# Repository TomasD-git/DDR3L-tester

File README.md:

# DDR3L-tester  
**Very simple DDR3L tester, plug ddr3l stick into slot, esp32 c6 reads data and can overwrite config of ram as well, with buttons for control and screen to see progress**  

<details>
<summary>How to make one?</summary>
  
**Either buy PCBA which is much easier but much more expenisve, or buy all parts and assemble with hotplate or hotair gun. all files needed for this are in production folder**  

</details>

<details>
<summary>How assemble?</summary>
Place top part ontop of the pcb and solder screen and buttons, then place the bottom part underneath the pcb and use M2 screws to screw into place.  

</details>

<details>
<summary>How to flash?</summary>
Plug the USB-C into computer and use arduino ide to flash.  

</details>

<details>
<summary>BOM</summary>

| Name | Purpose | Quantity | Total Cost (USD) | Link | Distributor |
| --- | --- | --- | --- | --- | --- |
| PCB + stencil if needed | all components are on this | 1 | 20 | https://jlcpcb.com | jlcpcb |
| ALL components | all components that are on pcb | 1 | 40 | https://lcsc.com | lcsc |
| Screen | shows info numbers etc.. | 1 | 3 | https://www.aliexpress.com/item/1005006141235306.html | Aliexpress |
| | | **Total cost** | **63** | | |

</details>

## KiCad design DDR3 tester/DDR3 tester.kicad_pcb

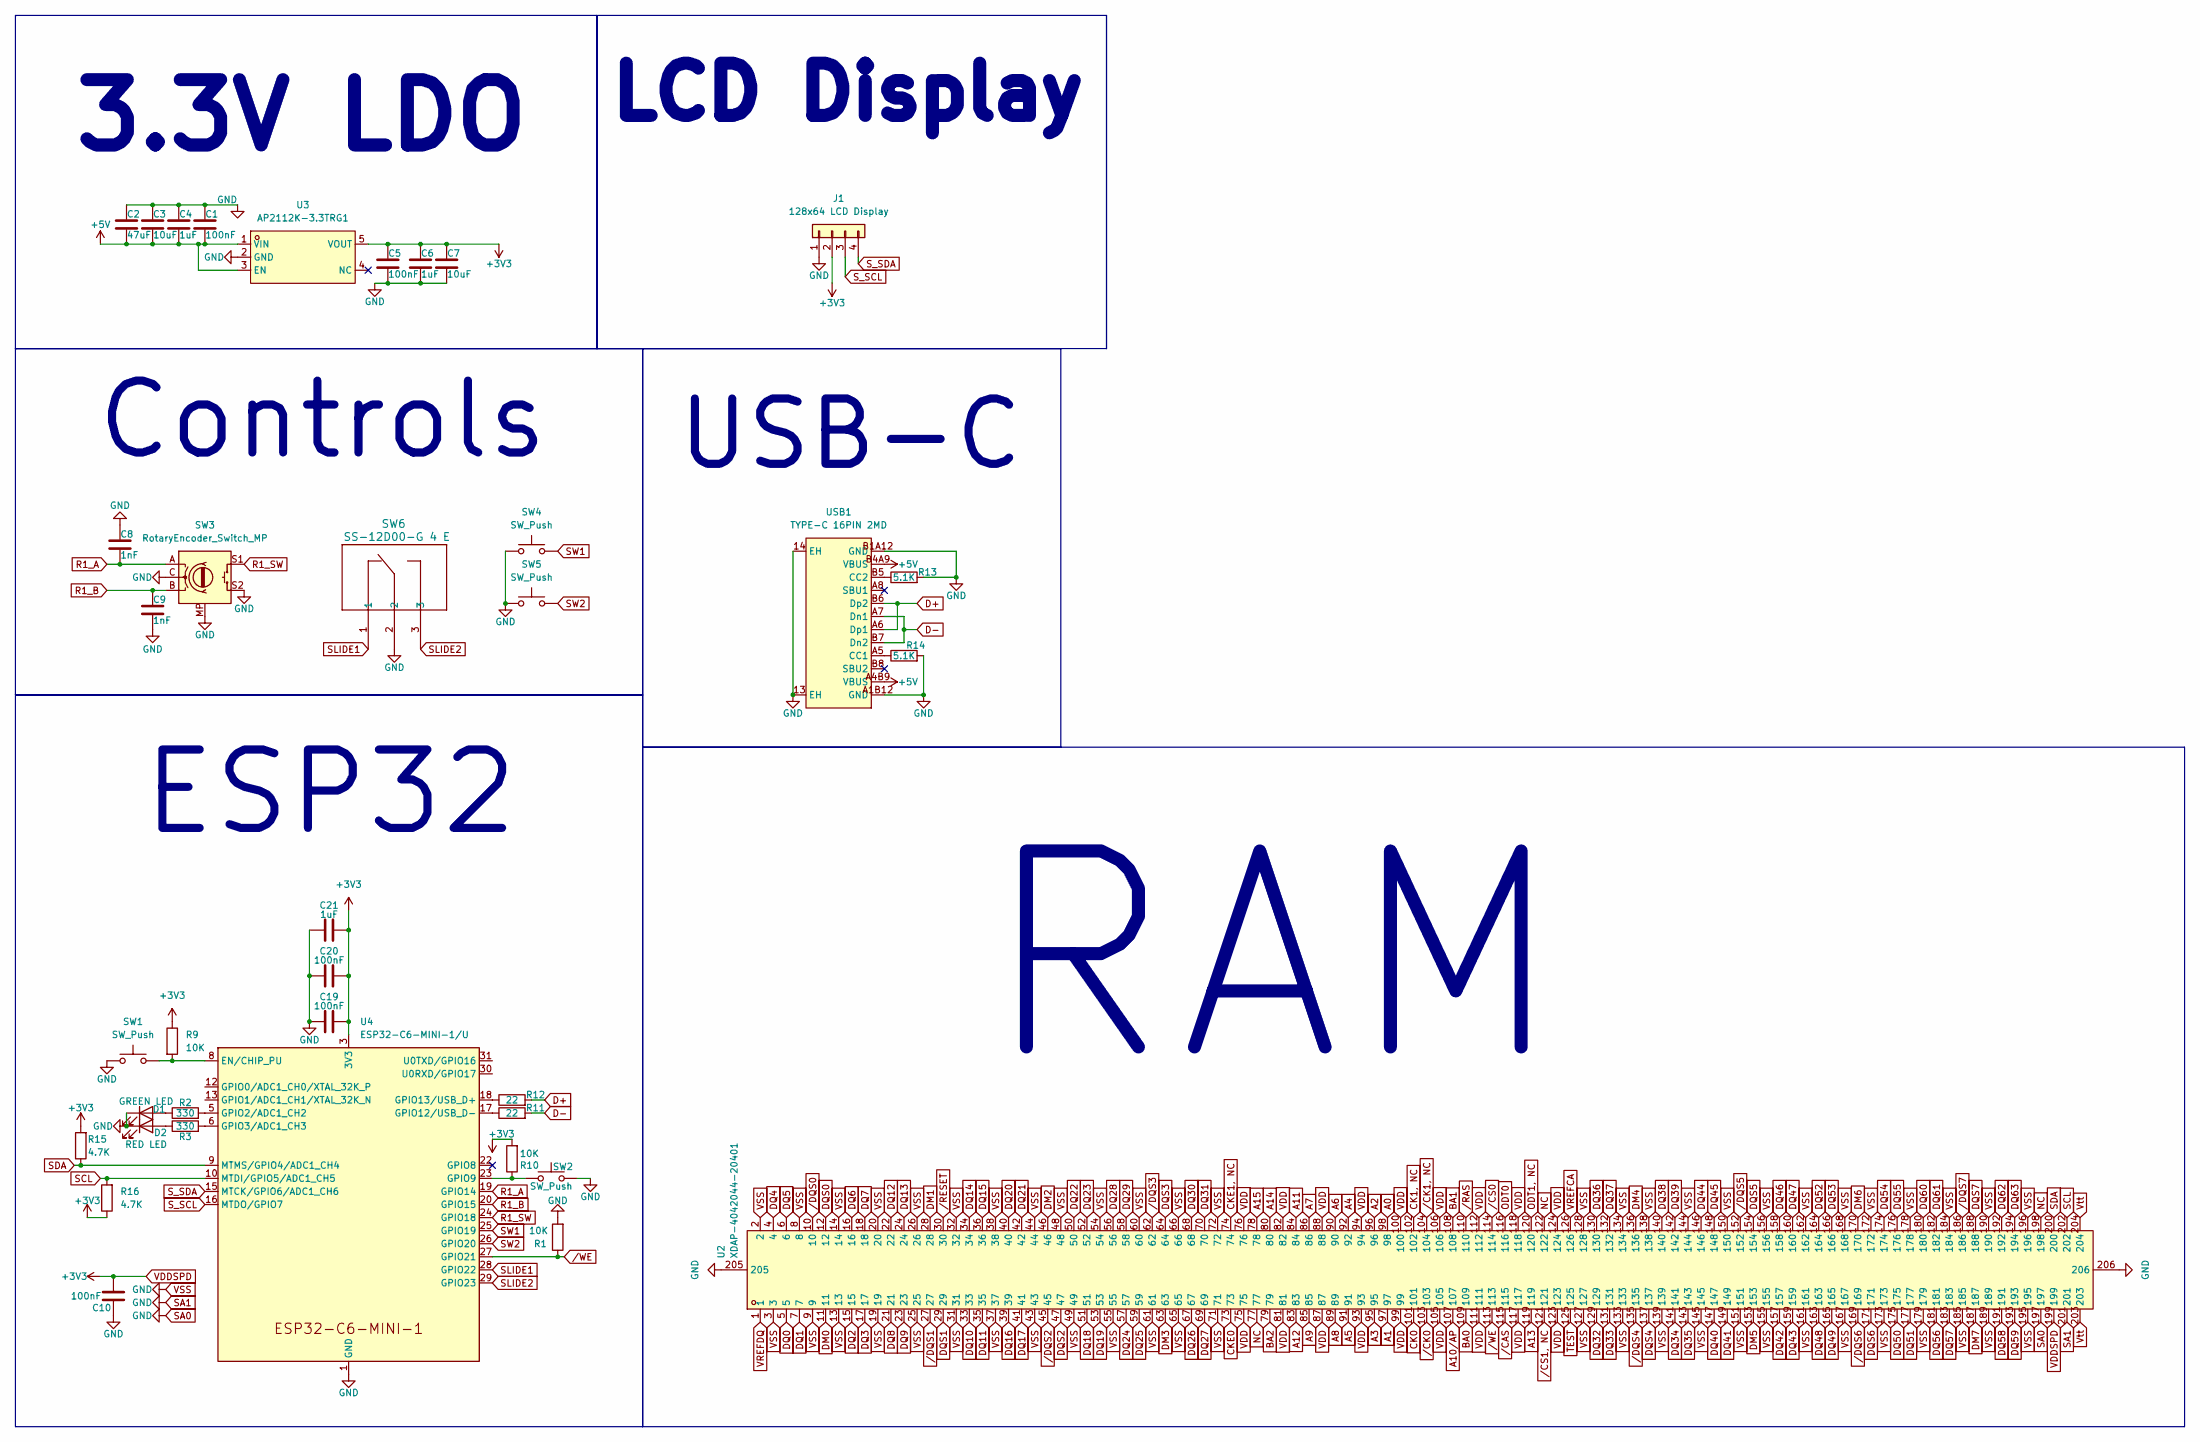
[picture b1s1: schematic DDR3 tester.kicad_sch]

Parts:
C1, C5, C10, C19, C20: 100nF; C_0805_2012Metric
C2: 47uF; C_1210_3225Metric
C3, C7: 10uF; C_0805_2012Metric
C4, C6, C21: 1uF; C_0805_2012Metric
C8, C9: 1nF; C_0805_2012Metric
D1: GREEN LED; LED_D5.0mm
D2: RED LED; LED_D5.0mm
J1: 128x64 LCD Display; PinSocket_1x04_P2.54mm_Vertical
R1, R9, R10: 10K; R_0805_2012Metric
R2, R3: 330; R_0805_2012Metric
R11, R12: 22; R_0805_2012Metric
R13, R14: 5.1K; R_0805_2012Metric
R15, R16: 4.7K; R_0805_2012Metric
SW1, SW2: SW_Push; SW_PUSH_6mm
SW3: RotaryEncoder_Switch_MP; RotaryEncoder_Alps_EC11E-Switch_Vertical_H20mm
SW4, SW5: SW_Push; SW_Cherry_MX_1.00u_PCB
SW6: SS-12D00-G 4 E; 1P2T_SS-12D00_CNK
U2: XDAP-4042044-20401; CONN-SMD_204P-P0.60_XDAP-4042044-20401; MPN XDAP-4042044-20401; LCSC Part C22471982
U3: AP2112K-3.3TRG1; SOT-25-5_L2.9-W1.6-P0.95-LS2.8-BL; MPN AP2112K-3.3TRG1; LCSC Part C51118
U4: ESP32-C6-MINI-1/U; ESP32-C6-MINI-1
USB1: TYPE-C 16PIN 2MD; USB-C-SMD_TYPE-C-16PIN-2MD-073; MPN TYPE-C 16PIN 2MD(073); LCSC Part C2765186

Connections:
+5V: C1.2, C2.1, C3.1, C4.2, U3.1 (VIN), U3.3 (EN), USB1.A4B9 (VBUS), USB1.B4A9 (VBUS)
A0: U2.98
A1: U2.97
A2: U2.96
A3: U2.95
A4: U2.92
A5: U2.91
A6: U2.90
A7: U2.86
A8: U2.89
A9: U2.85
A10/AP: U2.107
A11: U2.84
A12: U2.83
A13: U2.119
A14: U2.80
A15: U2.78
BA0: U2.109
BA1: U2.108
BA2: U2.79
CK0: U2.101
CK1, NC: U2.102
CKE0: U2.73
CKE1, NC: U2.74
D+: R12.2, USB1.A6 (Dp1), USB1.B6 (Dp2)
D-: R11.2, USB1.A7 (Dn1), USB1.B7 (Dn2)
DM0: U2.11
DM1: U2.28
DM2: U2.46
DM3: U2.63
DM4: U2.136
DM5: U2.153
DM6: U2.170
DM7: U2.187
DQ0: U2.5
DQ1: U2.7
DQ2: U2.15
DQ3: U2.17
DQ4: U2.4
DQ5: U2.6
DQ6: U2.16
DQ7: U2.18
DQ8: U2.21
DQ9: U2.23
DQ10: U2.33
DQ11: U2.35
DQ12: U2.22
DQ13: U2.24
DQ14: U2.34
DQ15: U2.36
DQ16: U2.39
DQ17: U2.41
DQ18: U2.51
DQ19: U2.53
DQ20: U2.40
DQ21: U2.42
DQ22: U2.50
DQ23: U2.52
DQ24: U2.57
DQ25: U2.59
DQ26: U2.67
DQ27: U2.69
DQ28: U2.56
DQ29: U2.58
DQ30: U2.68
DQ31: U2.70
DQ32: U2.129
DQ33: U2.131
DQ34: U2.141
DQ35: U2.143
DQ36: U2.130
DQ37: U2.132
DQ38: U2.140
DQ39: U2.142
DQ40: U2.147
DQ41: U2.149
DQ42: U2.157
DQ43: U2.159
DQ44: U2.146
DQ45: U2.148
DQ46: U2.158
DQ47: U2.160
DQ48: U2.163
DQ49: U2.165
DQ50: U2.175
DQ51: U2.177
DQ52: U2.164
DQ53: U2.166
DQ54: U2.174
DQ55: U2.176
DQ56: U2.181
DQ57: U2.183
DQ58: U2.191
DQ59: U2.193
DQ60: U2.180
DQ61: U2.182
DQ62: U2.192
DQ63: U2.194
DQS0: U2.12
DQS1: U2.29
DQS2: U2.47
DQS3: U2.64
DQS4: U2.137
DQS5: U2.154
DQS6: U2.171
DQS7: U2.188
NC: U2.77, U2.122, U2.198
unnamed: D1.2 (A), R2.1
unnamed: D2.2 (A), R3.1
unnamed: R9.2, SW1.2, U4.8 (EN/CHIP_PU)
unnamed: R2.2, U4.5 (GPIO2/ADC1_CH2)
unnamed: R3.2, U4.6 (GPIO3/ADC1_CH3)
unnamed: R10.1, SW2.1, U4.23 (GPIO9)
unnamed: R11.1, U4.17 (GPIO12/USB_D-)
unnamed: R12.1, U4.18 (GPIO13/USB_D+)
unnamed: R14.1, USB1.A5 (CC1)
unnamed: R13.1, USB1.B5 (CC2)
ODT0: U2.116
ODT1, NC: U2.120
R1_A: C8.2, SW3.A, U4.19 (GPIO14)
R1_B: C9.1, SW3.B, U4.20 (GPIO15)
R1_SW: SW3.S1, U4.24 (GPIO18)
SA0: C1.1, C2.2, C3.2, C4.1, C5.2, C6.2, C7.2, C8.1, C9.2, C10.1, C19.1, C20.1, C21.1, D1.1 (K), D2.1 (K), J1.1, R1.2, R13.2, R14.2, SW1.1, SW2.2, SW3.C, SW3.MP, SW3.S2, SW4.1, SW5.1, SW6.2, U2.2, U2.3, U2.8, U2.9, U2.13, U2.14, U2.19, U2.20, U2.25, U2.26, U2.31, U2.32, U2.37, U2.38, U2.43, U2.44, U2.48, U2.49, U2.54, U2.55, U2.60, U2.61, U2.65, U2.66, U2.71, U2.72, U2.127, U2.128, U2.133, U2.134, U2.138, U2.139, U2.144, U2.145, U2.150, U2.151, U2.155, U2.156, U2.161, U2.162, U2.167, U2.168, U2.172, U2.173, U2.178, U2.179, U2.184, U2.185, U2.189, U2.190, U2.195, U2.196, U2.197, U2.201, U2.205, U2.206, U3.2 (GND), U4.1 (GND), U4.2 (GND), U4.11 (GND), U4.14 (GND), U4.36 (GND), U4.37 (GND), U4.38 (GND), U4.39 (GND), U4.40 (GND), U4.41 (GND), U4.42 (GND), U4.43 (GND), U4.44 (GND), U4.45 (GND), U4.46 (GND), U4.47 (GND), U4.48 (GND), U4.49 (GND), U4.50 (GND), U4.51 (GND), U4.52 (GND), U4.53 (GND), USB1.13 (EH), USB1.14 (EH), USB1.A1B12 (GND), USB1.B1A12 (GND)
SCL: R16.2, U2.202, U4.10 (MTDI/GPIO5/ADC1_CH5)
SDA: R15.1, U2.200, U4.9 (MTMS/GPIO4/ADC1_CH4)
SLIDE1: SW6.1, U4.28 (GPIO22)
SLIDE2: SW6.3, U4.29 (GPIO23)
SW1: SW4.2, U4.25 (GPIO19)
SW2: SW5.2, U4.26 (GPIO20)
S_SCL: J1.3, U4.16 (MTDO/GPIO7)
S_SDA: J1.4, U4.15 (MTCK/GPIO6/ADC1_CH6)
TEST: U2.125
VDD: U2.75, U2.76, U2.81, U2.82, U2.87, U2.88, U2.93, U2.94, U2.99, U2.100, U2.105, U2.106, U2.111, U2.112, U2.117, U2.118, U2.123, U2.124
VDDSPD: C5.1, C6.1, C7.1, C10.2, C19.2, C20.2, C21.2, J1.2, R9.1, R10.2, R15.2, R16.1, U2.199, U3.5 (VOUT), U4.3 (3V3)
VREFCA: U2.126
VREFDQ: U2.1
Vtt: U2.203, U2.204
/CAS: U2.115
/CK0: U2.103
/CK1, NC: U2.104
/CS0: U2.114
/CS1, NC: U2.121
/DQS0: U2.10
/DQS1: U2.27
/DQS2: U2.45
/DQS3: U2.62
/DQS4: U2.135
/DQS5: U2.152
/DQS6: U2.169
/DQS7: U2.186
/RAS: U2.110
/RESET: U2.30
/WE: R1.1, U2.113, U4.27 (GPIO21)

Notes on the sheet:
RAM
LCD Display
Controls
USB-C
3.3V LDO
ESP32

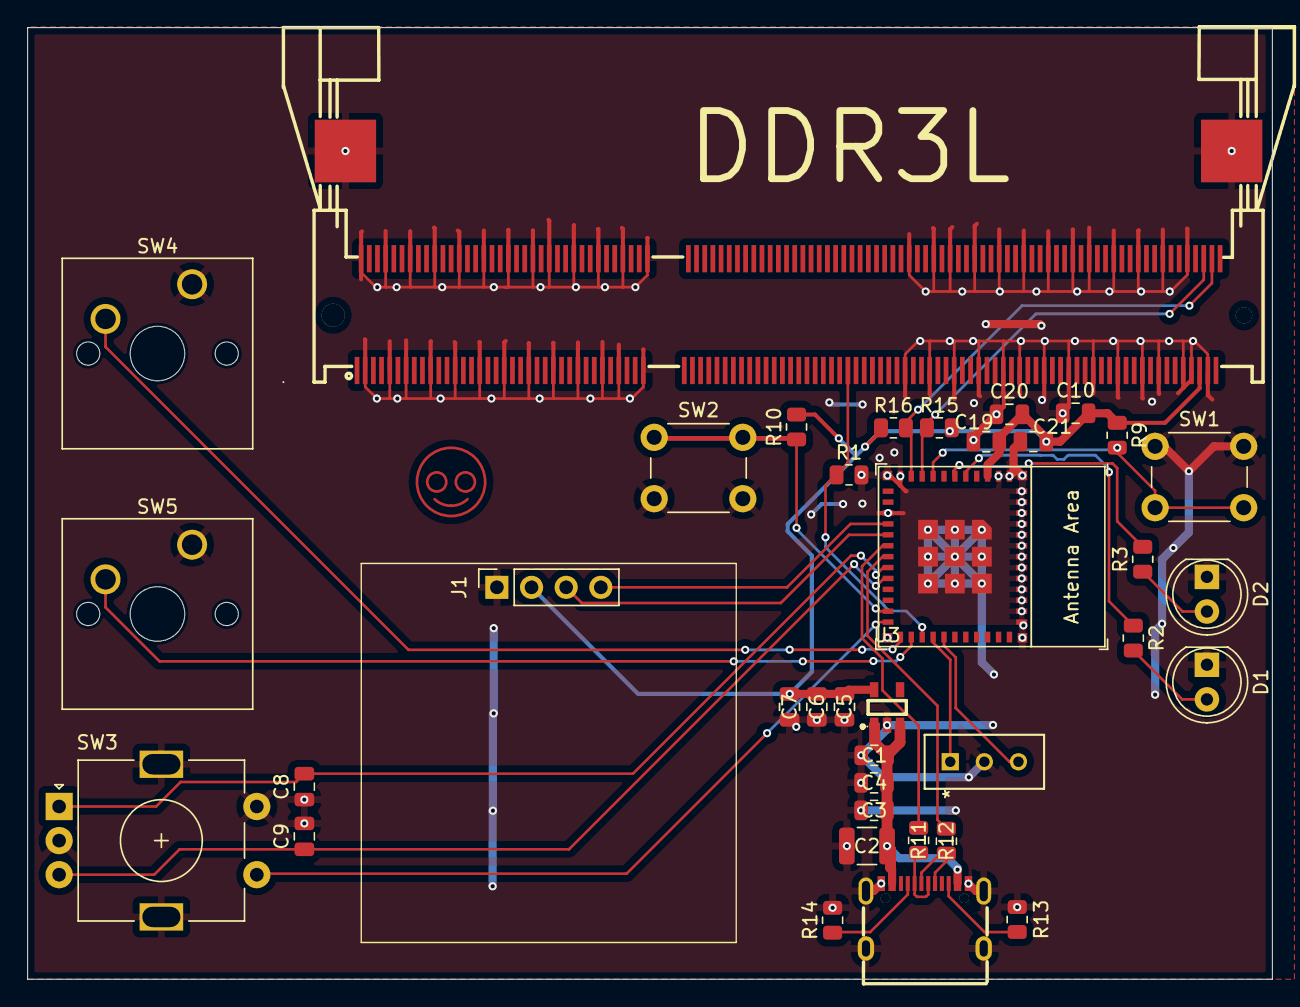
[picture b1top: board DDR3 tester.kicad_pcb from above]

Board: 2 copper layers, 91.3 x 69.8 mm, 37 parts (0 on the bottom side), 30 nets.

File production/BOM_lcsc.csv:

JLCPCB BOM Tool - BOM Matching,,,,,,,,,,,,,,,,,
BOM name：bom-JLCPCB Assembly Order.xlsx,,,Download Time：2026-06-09 15:07:55,,,,"* Our matching results are updated in real-time, but stock and prices may change. 
If it's been over 24 hours, please re-match before placing your order.",,,,,,,,,,
PCB Assembled Qty：5,,,Est. Total Price：46.1511,,,,,,,,,,,,,,
Your BOM,,,,,Matched Parts,,,,,,,Order Information,,,,,
Top Designator,Bottom Designator,Comment,Footprint,JLCPCB Part #,Matches,Part # ,Manufacturer,Footprint,Description,Category,Warning,JLCPCB Part #,Product link,Lib Type,Qty,Source,Total Price ($)
"C1,C10,C19,C20,C5",,100nF,0805,,Select by System,CC0805KRX7R9BB104,YAGEO,0805,100nF 50V X7R ±10% 0805 Multilayer Ceramic Capacitors MLCC - SMD/SMT ROHS,Multilayer Ceramic Capacitors MLCC - SMD/SMT,,C49678,https://jlcpcb.com/partdetail/YAGEO-CC0805KRX7R9BB104/C49678,Basic,35,35 JLCPCB,0.2975
C2,,47uF,1210,,Select by System,CS3225X7R476K100NRL,Samwha Capacitor,1210,10V 47uF X7R ±10% 1210 Multilayer Ceramic Capacitors MLCC - SMD/SMT ROHS,Multilayer Ceramic Capacitors MLCC - SMD/SMT,,C5189825,https://jlcpcb.com/partdetail/5869646-CS3225X7R476K100NRL/C5189825,Extended,9,9 JLCPCB,0.8595
"C3,C7",,10uF,0805,,Select by System,GRM21BR61H106KE43L,Murata Electronics,0805,10uF 50V X5R ±10% 0805 Multilayer Ceramic Capacitors MLCC - SMD/SMT ROHS,Multilayer Ceramic Capacitors MLCC - SMD/SMT,,C440198,https://jlcpcb.com/partdetail/439567-GRM21BR61H106KE43L/C440198,Basic,10,10 JLCPCB,3.083
"C8,C9",,1nF,0805,,Select by System,CL21B102KBCNNNC,Samsung Electro-Mechanics,0805,1nF 50V X7R ±10% 0805 Multilayer Ceramic Capacitors MLCC - SMD/SMT ROHS,Multilayer Ceramic Capacitors MLCC - SMD/SMT,,C46653,https://jlcpcb.com/partdetail/47657-CL21B102KBCNNNC/C46653,Basic,20,20 JLCPCB,0.224
"C21,C4,C6",,1uF,0805,,Select by System,CL21B105KBFNNNE,Samsung Electro-Mechanics,0805,1uF 50V X7R ±10% 0805 Multilayer Ceramic Capacitors MLCC - SMD/SMT ROHS,Multilayer Ceramic Capacitors MLCC - SMD/SMT,,C28323,https://jlcpcb.com/partdetail/29074-CL21B105KBFNNNE/C28323,Basic,25,25 JLCPCB,0.4325
D1,,GREENLED,LED_D5.0mm,,Select by Customer,TJ-L5FYTGHKMCGLFLC7K-A5,TOGIALED,"插件,D=5mm","-20℃~+80℃ 1.8V~2.6V 20mA 45° 565nm~575nm 575nm 5mm round lamp head 60mcd 72mW Green Diffused Lens Yellow Green 插件,D=5mm LED Indication - Discrete ROHS",LED Indication - Discrete,,C330740,https://jlcpcb.com/partdetail/TOGIALED-TJ_L5FYTGHKMCGLFLC7KA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,Extended,6,6 JLCPCB,0.2502
D2,,REDLED,LED_D5.0mm,,Select by Customer,333-2SURD/S530-A3,Everlight Elec,"插件,D=5mm","-40℃~+85℃ 200mcd 20mA 2V 30° 5mm round lamp head 624nm 632nm Red Red Lens 插件,D=5mm LED Indication - Discrete ROHS",LED Indication - Discrete,,C87271,https://jlcpcb.com/partdetail/EverlightElec-333_2SURD_S530A3/C87271,Extended,10,10 JLCPCB,0.417
"R1,R10,R9",,10K,0805,,Unconfirmed,0805W8F1002T5E,UNI-ROYAL(Uniroyal Elec),0805,-55℃~+155℃ 10kΩ 125mW 150V Thick Film Resistor ±1% ±100ppm/℃ 0805 Chip Resistor - Surface Mount ROHS,Chip Resistor - Surface Mount,1.The comment (0805W8F1002T5E) of this part does not match the one (10K) provided in your BOM. Please confirm;,C17414,https://jlcpcb.com/partdetail/18102-0805W8F1002T5E/C17414,Basic,25,25 JLCPCB,0.0725
"R2,R3",,330,0805,,Unconfirmed,0805W8F3300T5E,UNI-ROYAL(Uniroyal Elec),0805,-55℃~+155℃ 125mW 150V 330Ω Thick Film Resistor ±1% ±100ppm/℃ 0805 Chip Resistor - Surface Mount ROHS,Chip Resistor - Surface Mount,1.The comment (0805W8F3300T5E) of this part does not match the one (330) provided in your BOM. Please confirm;,C17630,https://jlcpcb.com/partdetail/18318-0805W8F3300T5E/C17630,Basic,20,20 JLCPCB,0.054
"R11,R12",,22,0805,,Unconfirmed,0805W8F220JT5E,UNI-ROYAL(Uniroyal Elec),0805,-55℃~+155℃ 125mW 150V 22Ω Thick Film Resistor ±1% ±100ppm/℃ 0805 Chip Resistor - Surface Mount ROHS,Chip Resistor - Surface Mount,1.The comment (0805W8F220JT5E) of this part does not match the one (22) provided in your BOM. Please confirm;,C17561,https://jlcpcb.com/partdetail/18249-0805W8F220JT5E/C17561,Basic,20,20 JLCPCB,0.054
"R13,R14",,5.1K,0805,,Unconfirmed,0805W8F5101T5E,UNI-ROYAL(Uniroyal Elec),0805,-55℃~+155℃ 125mW 150V 5.1kΩ Thick Film Resistor ±1% ±100ppm/℃ 0805 Chip Resistor - Surface Mount ROHS,Chip Resistor - Surface Mount,1.The comment (0805W8F5101T5E) of this part does not match the one (5.1K) provided in your BOM. Please confirm;,C27834,https://jlcpcb.com/partdetail/28584-0805W8F5101T5E/C27834,Basic,20,20 JLCPCB,0.054
"R15,R16",,4.7K,0805,,Unconfirmed,0805W8F4701T5E,UNI-ROYAL(Uniroyal Elec),0805,-55℃~+155℃ 125mW 150V 4.7kΩ Thick Film Resistor ±1% ±100ppm/℃ 0805 Chip Resistor - Surface Mount ROHS,Chip Resistor - Surface Mount,1.The comment (0805W8F4701T5E) of this part does not match the one (4.7K) provided in your BOM. Please confirm;,C17673,https://jlcpcb.com/partdetail/18361-0805W8F4701T5E/C17673,Basic,20,20 JLCPCB,0.044
"SW1,SW2",,SW_Push,SW_PUSH_6mm,,Select by Customer,TC-00104-050E,HOOYA,"插件,6x6mm","2.5N 5mm 6mm 6mm Black No PC Pin Round Button SPST Through Hole Without Bracket Plugin,6x6mm Tactile Switches ROHS",Tactile Switches,,C2939600,https://jlcpcb.com/partdetail/HOOYA-TC_00104050E/C2939600,Extended,10,10 JLCPCB,0.229
SW3,,RotaryEncoder_Switch_MP,RotaryEncoder_Alps_EC11E-Switch_Vertical_H20mm,,Select by Customer,EC11E1834403,ALPSALPINE,插件,-40℃~+85℃ 10mA 5V Non-resettable Straight Support Two-phase output 插件 Rotary Encoders ROHS,Rotary Encoders,,C361165,https://jlcpcb.com/partdetail/ALPSALPINE-EC11E1834403/C361165,Extended,5,5 JLCPCB,10.1695
SW6,,SS-12D00-G4E,1P2T_SS-12D00_CNK,,Select by Customer,SS-12D00-G3,SOFNG,"插件-3P,8.8x3.9mm","-35℃~+75℃ 3.9mm 7.2mm 8.8mm Black PC Pin Rectangular Columnar SPDT Through Hole 插件-3P,8.8x3.9mm Slide Switches ROHS",Slide Switches,,C22355741,https://jlcpcb.com/partdetail/SOFNG-SS_12D00G3/C22355741,Extended,6,6 JLCPCB,0.351
U2,,XDAP-4042044-20401,CONN-SMD_204P-P0.60_XDAP-4042044-20401,,Select by System,XDAP-4042044-20401,Lian Xin Technology,SMD,204P 5.2mm DDR3 SO-DIMM Surface Mount SMD Memory Connector (DDR) ROHS,Memory Connector (DDR),,C22471982,https://jlcpcb.com/partdetail/24195375-XDAP_404204420401/C22471982,Extended,5,5 JLCPCB,7.78
U3,,AP2112K-3.3TRG1,SOT-25-5_L2.9-W1.6-P0.95-LS2.8-BL,,Select by System,AP2112K-3.3TRG1,Diodes Incorporated,SOT-25-5,"-40℃~+85℃@(Ta) 1 250mV@(600mA) 3.3V 50uVrms 55uA 600mA 65dB@(1kHz) 6V Fixed Over Current Protection、Thermal Shutdown、Enable control Positive SOT-25-5 Voltage Regulators - Linear, Low Drop Out (LDO) Regulators ROHS","Voltage Regulators - Linear, Low Drop Out (LDO) Regulators",,C51118,https://jlcpcb.com/partdetail/DiodesIncorporated-AP2112K_33T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,Extended,7,7 JLCPCB,1.1375
U4,,ESP32-C6-MINI-1/U,ESP32-C6-MINI-1,,Select by Customer,ESP32-C6-MINI-1-N4,Espressif Systems,SMD-53P,-106dBm -40℃~+85℃ 2.4GHz 21dBm 354mA 3V~3.6V 71mA ESP32-C6FH4 On-board PCB Antenna UART、SPI、I2C、GPIO、I2S SMD-53P WiFi Modules ROHS,WiFi Modules,,C5736265,https://jlcpcb.com/partdetail/EspressifSystems-ESP32_C6_MINI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,Extended,5,5 JLCPCB,20.2015
USB1,,TYPE-C16PIN2MD,USB-C-SMD_TYPE-C-16PIN-2MD-073,,Select by System,TYPE-C 16PIN 2MD(073),SHOU HAN,SMD,"-25℃~+85℃ 1 16P 3A 5,000 times 5V Black Female Surface Mount, Right Angle Type-C SMD USB Connectors ROHS",USB Connectors,,C2765186,https://jlcpcb.com/partdetail/SHOUHAN-TYPE_C_16PIN_2MD_073/C2765186,Extended,6,6 JLCPCB,0.4404
J1,,128x64LCDDisplay,PinSocket_1x04_P2.54mm_Vertical,,No matches,No Part Selected,,,,,,,,,,,
"SW4,SW5",,SW_Push,SW_Cherry_MX_1.00u_PCB,,No matches,No Part Selected,,,,,,,,,,,

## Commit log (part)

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2026-06-09 added files
2026-06-09 added BOM
2026-06-09 added firmware
2026-06-09 Enhance README with assembly details and images
    Expanded the README to include assembly options and images.
2026-06-16 added CAD file
2026-06-16 added CAD files
